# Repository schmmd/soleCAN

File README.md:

# CAN tooling for Solectrac tractors

J1939 CAN-bus tooling for a Solectrac electric tractor.

## Repository map

| Path | What it is |
| --- | --- |
| `solecan-analyze.py` | Offline batch decoder: CAN log → tidy CSVs. |
| `solecan-stream.py` | Live / replay dashboard. |
| `solecan_proto.py` | Shared J1939 decode core (SA/PGN map, scalings) — single source of truth for both tools. |
| `dashboard.html` | The canonical HTML dashboard; used by solecan-stream.py, the firmware, and Android app. |
| `bms/` | UDS diagnostics for the BMS port (separate bus). |
| `esp32-s3/` | ESP32-S3 firmware: WiFi dashboard, JSON, BLE, USB SLCAN, socketcand. |
| `android/` | Android app that mirrors the ESP32 dashboard over BLE. |
| `DOCUMENTATION.md` | Main-bus J1939 decode, CAN topology, OBD-II pinout, cluster hardware, vendor error-code tables. |

## Python tooling

Dependencies live in `pyproject.toml` (managed with `uv`). The base install
(`python-can`, `pyserial`, `rich`) is enough for the analyzer and stream TUI;
the `ble` and `canalyst` extras add `bless` and `canalystii` for the embedded
BLE work and the Canalyst-II adapter respectively, and `all` pulls in both.

```sh
uv sync                          # base
uv sync --extra all              # everything
pip install .                    # base, via pip
pip install '.[ble,canalyst]'    # everything, via pip
```

### `solecan-analyze.py` — offline decoder

```sh
python3 solecan-analyze.py [-o OUTDIR] file1.asc [file2.blf ...]
```

Inputs are read via `python-can`'s `LogReader`, so any format `python-can`
understands works: `.asc` (Vector ASCII), `.blf`, `.log` (canutils), `.trc`,
and python-can's own `.csv` format.

Outputs four CSVs (regenerated on each run) that together let you trace any
decoded value back to its source bytes and the formula that produced it:

* `signals.csv` — what we decoded (one row per scalar)
* `frames.csv` — what was on the bus (one row per consumed frame, joined to
  signals via `frame_index`)
* `decoders.csv` — how we decoded it (per-signal formula catalog)
* `can_ids.csv` — every unique CAN ID seen, with J1939 breakdown

To re-derive a value by hand: pick a row from `signals.csv`, look up its
`frame_index` in `frames.csv` to get the raw bytes, then look up its `signal`
in `decoders.csv` for the formula.

#### `signals.csv` — tidy long-format measurements

```
file, timestamp, frame_index, signal, value, unit
```

In [tidy / long format][tidy]. Pivot to wide from any consumer:

```python
import pandas as pd
df = pd.read_csv("signals.csv")
wide = df.pivot_table(index="timestamp", columns="signal", values="value")
```

Signal names use a `domain.name` (or `domain.NN.name`) convention —
`cell.NN.voltage_v`, `pack.voltage_v`, `motor.rpm_signed`, `bms.fault.code_NNN`,
`dm1.dtc.spn`, etc. The complete list with formulas, byte positions, and
confidence levels lives in `decoders.csv` (generated from the `DECODERS`
table in `solecan-analyze.py`); the decode itself is in `solecan_proto.py`.

[tidy]: https://vita.had.co.nz/papers/tidy-data.pdf

#### `frames.csv` — raw frame log

```
frame_index, file, timestamp, can_id, pgn, source, len, b0, b1, b2, b3, b4, b5, b6, b7
```

`can_id` is 8-hex (e.g. `18F100F3`), `pgn` is 4-hex, `source` is 2-hex,
each `bN` is the data byte at position N as 2-hex. One row per frame that
produced at least one signal.

#### `decoders.csv` — per-signal decode rule catalog

```
signal, pgn, source, bytes, formula, unit, confidence, notes
```

One row per signal name (parametric signals like `cell.NN.voltage_v` use
`NN` as a placeholder). `bytes` references positions within `frames.csv`'s
`b0..b7` columns. `confidence` is `verified`, `tentative`, or `unknown`.

#### `can_ids.csv` — per-unique-CAN-ID J1939 decode

```
id, ext, count, priority, R, DP, PF, PS, SA, PGN, PDU, PS_role, name
```

### `solecan-stream.py` — live dashboard

Live (or replayed) BMS / charger / motor dashboard. Decodes the same J1939
frames as `solecan-analyze.py` and serves a dashboard.

```sh
# Live capture using slcan
solecan-stream.py --interface slcan --channel /dev/cu.usbmodem101 --bitrate 250000

# Live capture using socketcan
solecan-stream.py --interface socketcan --channel can0 --bitrate 250000

# Replay an existing capture
solecan-stream.py --replay session.log
```

Displays pack voltage / current / DC and estimated AC power, BMS-published
SOC, charger output, per-cell voltages
with min/max/spread, module temperatures, vehicle-controller heartbeat, and
live alerts (low/high cell, spread, temp, AC budget, stale BMS).

### `bms/` — UDS diagnostics dashboard

Polls UDS Data Identifiers on the BMS's separate 2-pin diagnostic port in a
background thread and serves a localhost dashboard. Independent of the
main-bus tools and `solecan_proto.py`; its DID map lives in
[`bms/README.md`](bms/README.md).

```sh
python3 bms/solectrac-bms-diagnostics.py
```

## Embedded firmware — `esp32-s3/`

ESP32-S3 firmware that re-implements the main-bus J1939 decode in C++ and
exposes it as a WiFi dashboard, JSON endpoint, BLE, USB SLCAN, and socketcand.
Supports the RejsaCAN, LilyGo T-2CAN, and Adafruit Feather S3. Build, wiring,
and flashing are in [`esp32-s3/README.md`](esp32-s3/README.md).

## Android app — `android/`

Mirrors the ESP32 dashboard over BLE so the phone doesn't need to join the
tractor's WiFi. See [`android/README.md`](android/README.md).

## Disclaimer

This is a personal exercise based on observed CAN traffic. PGN meanings are
inferred from data and may be wrong.

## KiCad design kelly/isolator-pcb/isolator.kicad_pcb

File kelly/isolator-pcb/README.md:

# Kelly UART isolator PCB

A galvanic isolator dongle between the Kelly KLS7218M SM-4P port (floating,
traction-pack referenced) and the OBD-powered RejsaCAN. Electrical design
rationale, part choices, and behavior notes live in `../ISOLATOR.md`; this
directory only adds the board.

## Files

- `generate_board.py` — writes `isolator.kicad_pcb` from scratch. The script
  is the source of truth; edit it and re-run rather than editing the board in
  KiCad (or fork the `.kicad_pcb` if you prefer the GUI from here on).
  Output is deterministic — tstamp UUIDs are derived from the element each
  one belongs to, so re-running with no changes produces a byte-identical
  file and a real edit shows up in the diff as itself, not as 187 churned
  UUIDs.
- `isolator.kicad_pcb` — generated KiCad board (opens in KiCad 7+).
- `gerbers/` — fab outputs (RS-274X + Excellon), exported with KiCad 10
  `kicad-cli`. Zip the directory (command below) and upload to JLCPCB/PCBWay/
  OSH Park. 2-layer, 50 x 32 mm, 1.6 mm, any finish; no special options.
- `render_top.png` / `render_bottom.png` — 3D renders for a quick look.

Regenerate everything:

```bash
python3 generate_board.py
KICLI=/Applications/KiCad/KiCad.app/Contents/MacOS/kicad-cli
$KICLI pcb drc --severity-error isolator.kicad_pcb
$KICLI pcb export gerbers --layers F.Cu,B.Cu,F.Mask,B.Mask,F.SilkS,B.SilkS,Edge.Cuts -o gerbers/ isolator.kicad_pcb
$KICLI pcb export drill --format excellon --excellon-units mm --generate-map --map-format gerberx2 -o gerbers/ isolator.kicad_pcb
(cd gerbers && zip -q ../isolator-gerbers.zip isolator-*.gb* isolator-*.gt* isolator.drl)
$KICLI pcb render --side top    --zoom 1.0 --width 1400 --height 950 --quality high -o render_top.png    isolator.kicad_pcb
$KICLI pcb render --side bottom --zoom 1.0 --width 1400 --height 950 --quality high -o render_bottom.png isolator.kicad_pcb
```

## Generate-time checks

`generate_board.py` asserts these on every run, against the emitted board
rather than its own variables:

- **U1 pads match the ADuM1201 pinout** (`ADUM1201`, transcribed from
  datasheet Rev. L Fig. 5).
- **Package shape**: supplies on pins 1/8, grounds on 4/5, signals on
  2/3/6/7. This is a *different* statement than "Fig. 5 says X", so it still
  fires if the transcription itself is wrong — which is the hole rev A fell
  through. Rev A's pinout fails it.
- **Isolation barrier**: no copper of a Kelly-domain net may reach the
  chassis-domain side or vice versa. Measures the gap and requires ≥ 3.5 mm;
  currently 3.80 mm.
- **Nothing dangling**: every net lands on at least two pads.

What none of them catch: a wrong fact that is wrong everywhere. If the
datasheet transcription and the package-shape rule were both wrong in the
same direction, the board would still be wrong. The defence against that is
a meter on a physical board: the GND1-to-GND2 open check in
`../ISOLATOR.md` "Power-up check".

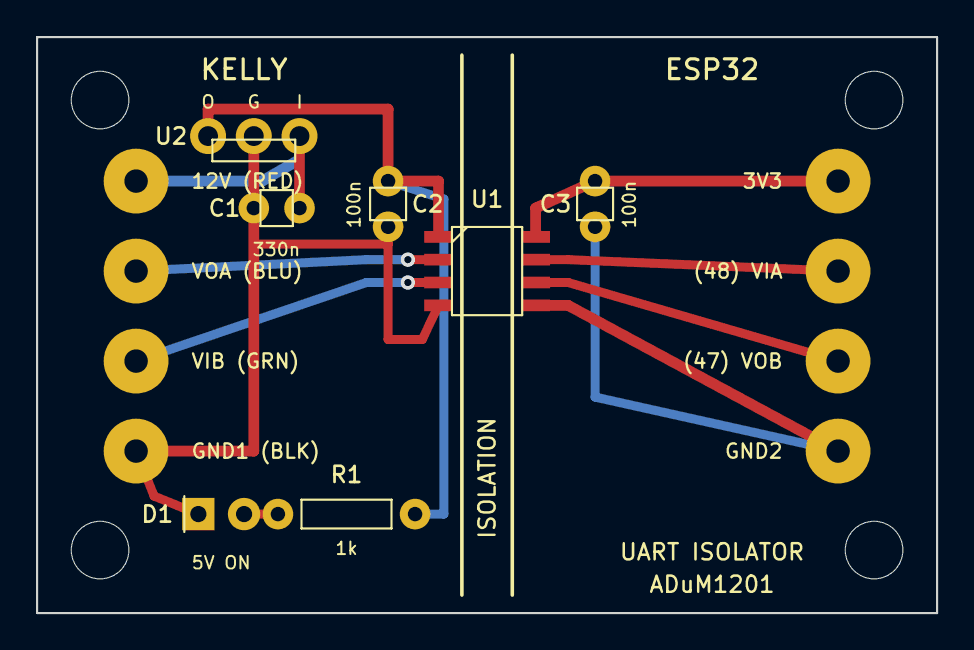
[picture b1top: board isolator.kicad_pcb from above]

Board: 2 copper layers, 50.0 x 32.0 mm, 19 parts (0 on the bottom side), 10 nets.

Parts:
C1, C2, C3: C_disc_2.54
D1: LED_5mm
H1, H2, H3, H4: Hole_3.2_NPTH
J1, J2, J3, J4, J5, J6, J7, J8: WirePad_3.6mm
R1: R_axial_7.62
U1: SOIC-8_ADuM1201
U2: TO-92_78L05

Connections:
+3V3: C3.1, J5.1, U1.8
+5V_K: C2.1, R1.1, U1.1, U2.1
+12V_K: C1.1, J1.1, U2.3
GND1: C1.2, C2.2, D1.2, J4.1, U1.4, U2.2
GND2: C3.2, J8.1, U1.5
LED_K: D1.1, R1.2
VIA: J6.1, U1.7
VIB: J3.1, U1.3
VOA: J2.1, U1.2
VOB: J7.1, U1.6

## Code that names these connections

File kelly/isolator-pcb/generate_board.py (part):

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
  KELLY SIDE (floating, 5 V)     | barrier |   BOARD SIDE (chassis, 3.3 V)
  RED  12V -> 78L05 -> 5V -> VDD1|1       8|VDD2 <- 3V3
  BLU  Kelly Rx <------------ VOA|2       7|VIA  <- GPIO48 (TX)
  GRN  Kelly Tx ------------- VIB|3       6|VOB  -> GPIO47 (RX)
  BLK  V-  ------------------GND1|4       5|GND2 <- GND

No copper crosses the vertical isolation gap except the ADuM1201 itself.
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
# net table: number -> name. Signal nets use the ADuM1201 pin names so the
# direction is unambiguous: VIB = Kelly Tx into the chip, VOA = out to Kelly
# Rx (both floating); VIA = GPIO48 into the chip, VOB = out to GPIO47 (both
# chassis side). Colors / GPIO numbers appear only on silk.
NETS = {
    1: "+12V_K", 2: "GND1", 3: "+5V_K", 4: "VIB", 5: "VOA",
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P_VOA = (5.5, 13.0)
P_VIB = (5.5, 18.0)
P_BLK = (5.5, 23.0)
# Board-side wire pads (right edge column); VIA = GPIO48, VOB = GPIO47
P_3V3 = (44.5, 8.0)
P_VIA = (44.5, 13.0)
P_VOB = (44.5, 18.0)
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U1_R = 27.7   # pins 5-8 (board/side-2) column
U1 = {  # pin -> (x, y, net)
    1: (U1_L, UY + PIN_DY[0], 3),   # VDD1 <- 5V
    2: (U1_L, UY + PIN_DY[1], 5),   # VOA  -> Kelly Rx (BLU)
    3: (U1_L, UY + PIN_DY[2], 4),   # VIB  <- Kelly Tx (GRN)
    4: (U1_L, UY + PIN_DY[3], 2),   # GND1
    5: (U1_R, UY + PIN_DY[3], 7),   # GND2
    6: (U1_R, UY + PIN_DY[2], 8),   # VOB  -> GPIO47
    7: (U1_R, UY + PIN_DY[1], 9),   # VIA  <- GPIO48
    8: (U1_R, UY + PIN_DY[0], 6),   # VDD2 <- 3V3
}

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route([(19.5, 11.5), (19.5, 14.905), U1[4][:2]], 2, "F.Cu", TRACE_SIG)
# C1A -> U2 IN (12V)
route([C1_A, U2_IN], 1, "F.Cu", TRACE_PWR)
# VOA (chip out -> Kelly Rx, blue): bottom to via, top stub into pin 2
route([P_VOA, (18.3, 12.365), VIA_VOA], 5, "B.Cu", TRACE_SIG)
via(VIA_VOA, 5)
route([VIA_VOA, U1[2][:2]], 5, "F.Cu", TRACE_SIG)
# VIB (Kelly Tx -> chip in, green): bottom to via, top stub into pin 3
route([P_VIB, (18.3, 13.635), VIA_VIB], 4, "B.Cu", TRACE_SIG)
via(VIA_VIB, 4)
route([VIA_VIB, U1[3][:2]], 4, "F.Cu", TRACE_SIG)
# +3V3: pad -> C3A -> VDD2 (pin 8)
route([P_3V3, C3_A, (27.7, 9.5), U1[8][:2]], 6, "F.Cu", TRACE_PWR)
# VIA (GPIO48 -> chip in): pad -> pin 7
route([P_VIA, (29.5, 12.365), U1[7][:2]], 9, "F.Cu", TRACE_SIG)
# VOB (chip out -> GPIO47): pad -> pin 6
route([P_VOB, (29.5, 13.635), U1[6][:2]], 8, "F.Cu", TRACE_SIG)
# GND2: pad -> GND2 (pin 5) on top; C3B joins on bottom
route([P_GND, (29.5, 14.905), U1[5][:2]], 7, "F.Cu", TRACE_PWR)
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
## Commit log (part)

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2026-06-06 Consolidate more logic into solectrac_proto.py
2026-06-07 Update documentation with SOC 30, 20, 10 and gimp mode captures.
2026-06-07 Change the bms dashboard to stream data when replaying.
2026-06-07 Update with data from a long 110 V charge session.
2026-06-07 Update bms-diagnostics with analysis from the long charge capture.
2026-06-08 Add amperage limit to dashboard.
2026-06-08 Replace speed with rpm and add tick marks.
2026-06-08 Several small improvements.
2026-06-08 Rename throttle to torque.
2026-06-08 Show error codes in a single red section.
2026-06-08 Remove the DBC file as it's certainly out of date and I have no need for it. I can recreate it later if needed.
2026-06-08 Decode F107
2026-06-08 Update documentation for a byte that's not always 0.
2026-06-08 Update to BMS docs.
2026-06-09 Remove the starting... status.
2026-06-09 Rename standby to plug
2026-06-09 Close some open questions.
2026-06-09 Improve BMS README.md
2026-06-10 Updates to documentation from fable.
2026-06-10 Fix the scripts in response to some of the docs improvements.
2026-06-10 Show a bitmap of charger states instead of text
2026-06-10 Always show the charger card.
2026-06-13 Add documentation for 12 v fuses.
2026-06-14 Add support for the second can port over socketcand.
2026-06-14 Update documentation from more dual captures.
2026-06-14 WIP dual can with esp32.
2026-06-14 Commit boards directory.
2026-06-15 Add send functionality to the esp32 firmware.
2026-06-15 Update documentation from iBMS exports.
2026-06-15 Make the home-network join optional (AP-only by default)
    The board runs a soft-AP and a station on one shared radio. When WIFI_SSID
    is empty the station would scan every channel forever for a network that
    isn't there, which makes the soft-AP beacon hop channels and drop out — the
    hotspot appears briefly, refuses clients, then vanishes. This was the
    behavior whenever no real bench network was configured.
    Gate the station on a configured SSID: with an empty WIFI_SSID the firmware
2026-06-16 Add clickable per-cell battery detail view to dashboard
2026-06-16 Sync firmware dashboard copy with per-cell detail view
2026-06-18 Add observed confirmation for accumulated discharge capacity.
2026-06-19 Add RejsaCAN support.
2026-06-19 Document LilyGo T-2CAN tractor wiring and power
    Add README sections for connecting the board to the tractor's OBD-II port
    (J1962 pins 6/14/4/16 -> CANH/CANL/GND on the CAN B / can0 terminal, plus why
    the ground wire is mandatory with the galvanically-isolated transceiver) and
    for powering it from the DC 5-12 V input -- including tapping the tractor's
    12 V rail for a single-cable field setup.
2026-06-19 Include per-cell arrays in BLE payload so detail view works over Bluetooth
    The minimal/BLE payload previously stripped pack.cells.voltages and
    temp_readings to save bandwidth, so the cell-detail view only worked over
    WiFi. Emit them in the minimal payload too (~200 B / a couple more BLE
    chunks) and reword the dashboard's empty-state message to be
    transport-agnostic (it now only shows before the first BMS frame).
2026-06-20 Move LilyGo information into a dedicated section.
2026-06-20 Add RejsaCAN support (#29)
2026-06-20 Add delta SOC to the session view.
2026-06-20 Add some files that were untracked.
2026-06-20 Add GitHub actions to make sure components build.
2026-06-20 Fix .dockerignore.
2026-06-20 Fix cell detail page on solecan-stream.py.
2026-06-20 Add Apache 2.0 LICENSE.txt.
2026-06-23 Add CAN_LISTEN_ONLY build flag for the LilyGo T-2CAN
    Tapping a bus shared with a device you must not disturb (e.g. a fleet or
    compliance telematics logger) is safer if this monitor never transmits. Add an
    opt-in -DCAN_LISTEN_ONLY build flag that puts the ESP32 TWAI controller in
    TWAI_MODE_LISTEN_ONLY: it emits no ACKs and no error frames, so it cannot
    perturb other nodes on the bus (beyond what CAN error-confinement already
    guarantees). The tractor's other nodes handle ACKing, so monitoring still works.
2026-06-23 Add a screenshot to the android README.
2026-06-23 Update documentation about data from a second tractor.
2026-06-23 Rework the cell detail page.
2026-06-23 A few scattered extensions (#34)
    * Add a screenshot to the android README.
    * Update documentation about data from a second tractor.
    * Rework the cell detail page.
2026-06-23 Move listen-only documention to a non-board specific location.
2026-06-23 AI pass on the README.md
2026-06-23 Some manual README improvements.
2026-06-23 Consolidate the requirements.txt and pyproject.toml.
2026-06-23 Add web screenshot.
2026-06-23 Change Dockerfile to not use requirements.txt
2026-06-23 Add CAN_LISTEN_ONLY build flag for the LilyGo T-2CAN (#33)
2026-06-24 Add versioning to the embedded and android code.
2026-06-30 Show the version in the web ui.
